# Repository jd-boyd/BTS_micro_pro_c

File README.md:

# BTS_micro_pro_c

## ABOUT

MCU board, mostly with pinout of Arduino Nano Pro, shows up as Leonardo, has USB-C connector.

## LICENSE

* Licensed under CERN-OHL-P v2 or later
* See LICENSE file
* See https://ohwr.org/project/cernohl/wikis/uploads/8a6b5d01f71c207c49493e4d114d61e6/cern_ohl_p_v2_howto.pdf for summary.

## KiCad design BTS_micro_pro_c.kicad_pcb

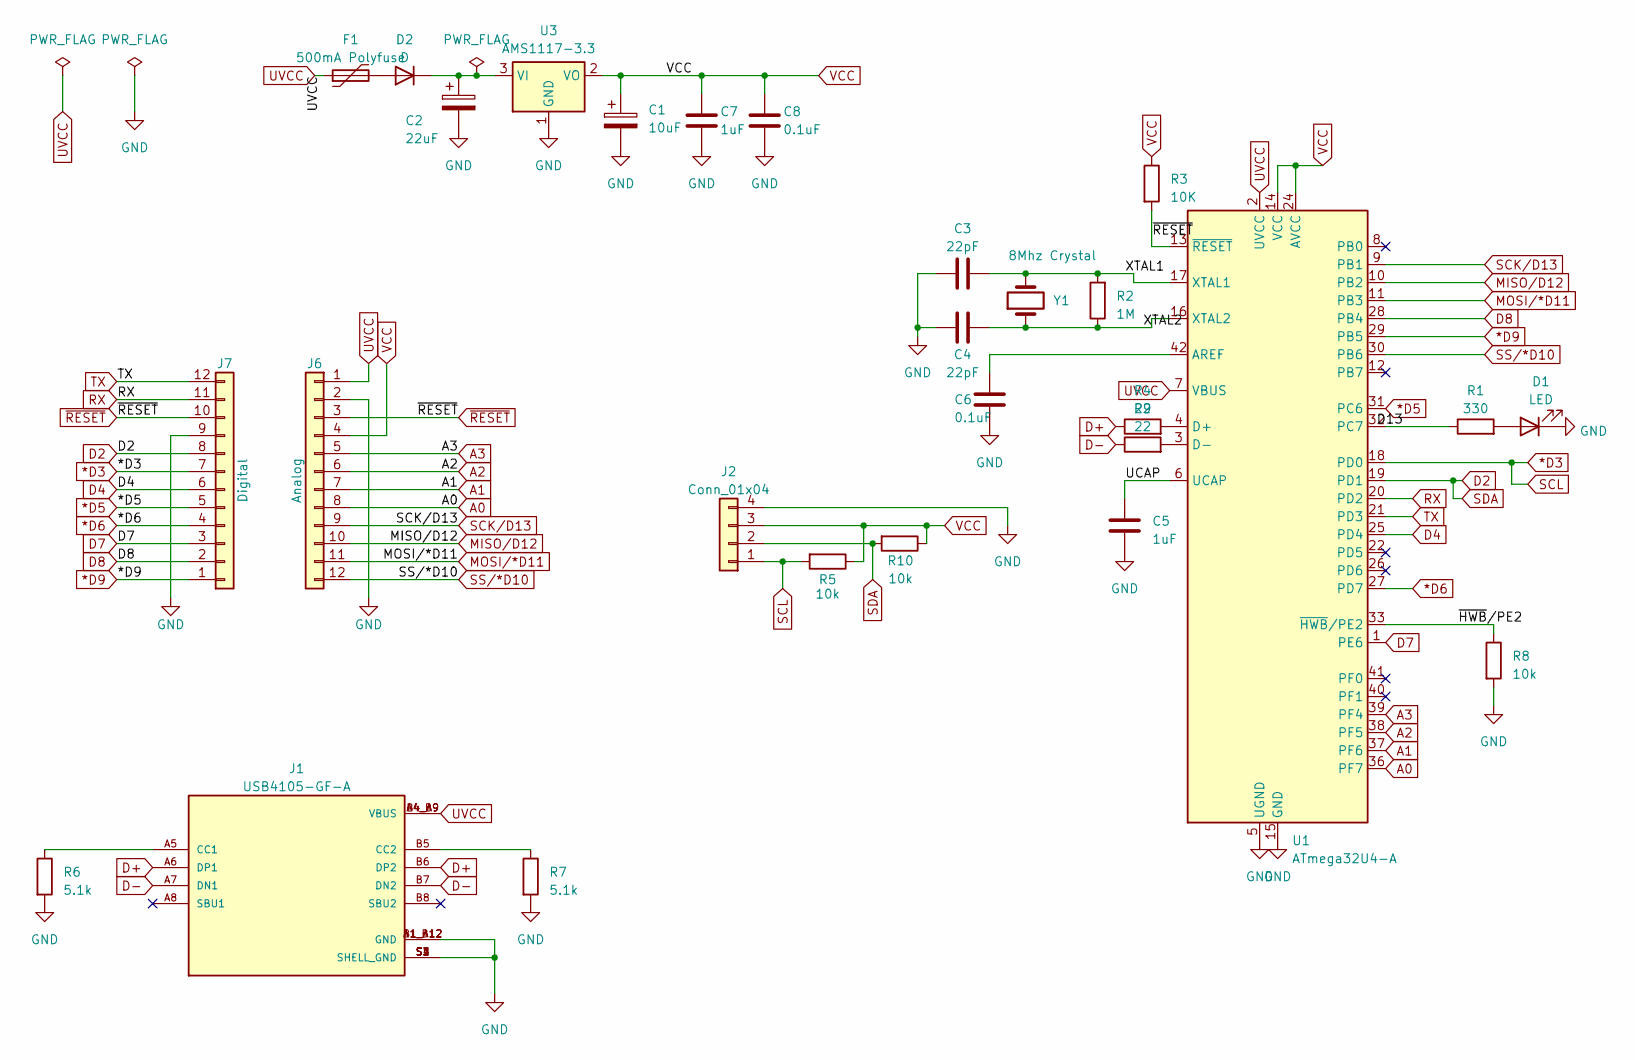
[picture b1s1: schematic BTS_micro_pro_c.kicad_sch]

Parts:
C1: 10uF; C_0402_1005Metric
C2: 22uF; C_0402_1005Metric
C3, C4: 22pF; C_0402_1005Metric
C5, C7: 1uF; C_0402_1005Metric
C6, C8: 0.1uF; C_0402_1005Metric
D1: LED; LED_0402_1005Metric
D2: D; D_0402_1005Metric; LCSC C316041
F1: 500mA Polyfuse; Fuse_0805_2012Metric; LCSC C135331
J1: USB4105-GF-A; GCT_USB4105-GF-A; PARTREV A3; LCSC C165948
J2: Conn_01x04; JST_SH_BM04B-SRSS-TB_1x04-1MP_P1.00mm_Vertical; LCSC C495539
J6: Analog; PinHeader_1x12_P2.54mm_Vertical
J7: Digital; PinHeader_1x12_P2.54mm_Vertical
R1: 330; R_0402_1005Metric
R2: 1M; R_0402_1005Metric
R3: 10K; R_0402_1005Metric
R4, R9: 22; R_0402_1005Metric
R5, R8, R10: 10k; R_0402_1005Metric
R6, R7: 5.1k; R_0402_1005Metric
U1: ATmega32U4-A; QFN-44-1EP_7x7mm_P0.5mm_EP5.2x5.2mm; LCSC C112161
U3: AMS1117-3.3; SOT-23-3; LCSC C5446
Y1: 8Mhz Crystal; Crystal_SMD_3225-2Pin_3.2x2.5mm; LCSC C409345

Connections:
*D3: J2.1, J7.7, R5.2, U1.18 (PD0)
*D5: J7.5, U1.31 (PC6)
*D6: J7.4, U1.27 (PD7)
*D9: J7.1, U1.29 (PB5)
/D13: R1.1, U1.32 (PC7)
/UCAP: C5.1, U1.6 (UCAP)
/XTAL1: C3.2, R2.2, U1.17 (XTAL1), Y1.2
/XTAL2: C4.1, R2.1, U1.16 (XTAL2), Y1.1
/~HWB/PE2: R8.1, U1.33 (~HWB/PE2)
A0: J6.8, U1.36 (PF7)
A1: J6.7, U1.37 (PF6)
A2: J6.6, U1.38 (PF5)
A3: J6.5, U1.39 (PF4)
D2: J2.2, J7.8, R10.2, U1.19 (PD1)
D4: J7.6, U1.25 (PD4)
D7: J7.3, U1.1 (PE6)
D8: J7.2, U1.28 (PB4)
D+: J1.A6 (DP1), J1.B6 (DP2), R4.1
D-: J1.A7 (DN1), J1.B7 (DN2), R9.1
GND: C1.2, C2.2, C3.1, C4.2, C5.2, C6.2, C7.2, C8.2, D1.1 (K), J1.A1_B12 (GND), J1.B1_A12 (GND), J1.S1 (SHELL_GND), J1.S2 (SHELL_GND), J1.S3 (SHELL_GND), J1.S4 (SHELL_GND), J2.4, J6.2, J7.9, R6.2, R7.2, R8.2, U1.5 (UGND), U1.15 (GND), U1.23 (GND), U1.35 (GND), U1.43 (GND), U3.1 (GND)
MISO/D12: J6.10, U1.10 (PB2)
MOSI/*D11: J6.11, U1.11 (PB3)
unnamed: D1.2 (A), R1.2
unnamed: D2.2 (A), F1.2
unnamed: C2.1, D2.1 (K), U3.3 (VI)
unnamed: J1.A5 (CC1), R6.1
unnamed: J1.B5 (CC2), R7.1
unnamed: C6.1, U1.42 (AREF)
unnamed: R4.2, U1.4 (D+)
unnamed: R9.2, U1.3 (D-)
RX: J7.11, U1.20 (PD2)
SCK/D13: J6.9, U1.9 (PB1)
SS/*D10: J6.12, U1.30 (PB6)
TX: J7.12, U1.21 (PD3)
UVCC: F1.1, J1.A4_B9 (VBUS), J1.B4_A9 (VBUS), J6.1, U1.2 (UVCC), U1.7 (VBUS)
VCC: C1.1, C7.1, C8.1, J2.3, J6.4, R3.1, R5.1, R10.1, U1.14 (VCC), U1.24 (AVCC), U1.34 (VCC), U1.44 (AVCC), U3.2 (VO)
~RESET: J6.3, J7.10, R3.2, U1.13 (~RESET)

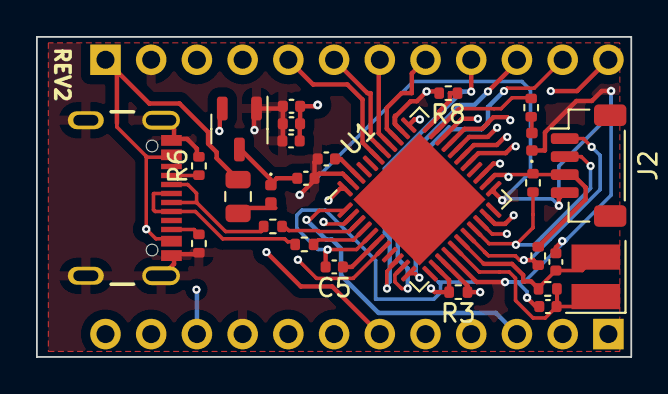
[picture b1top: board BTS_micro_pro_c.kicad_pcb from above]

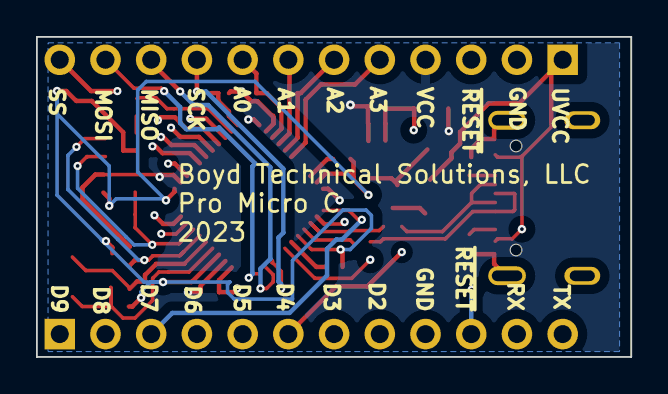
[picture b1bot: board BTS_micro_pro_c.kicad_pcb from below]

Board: 4 copper layers, 33.0 x 17.8 mm, 28 parts (2 on the bottom side), 37 nets.

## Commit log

2023-04-02 Change license to intented one.
2023-04-02 Initial import of KiCAD project.
2023-04-05 Placeholder for changes.
2023-04-05 Start datasheets directory, add cpu.
2023-04-08 More progress.
2023-04-11 Schematic potentially done, needs footprints assigned though.
2023-04-14 Finish rev1.
2023-04-21 Start rev 2.
    In schematic, add USB resistors, put back I2C port.
    Also, fix rotation issue that JLCPCB DFM picked up.
2023-04-25 Update project to rev 2.
    This includes new I2C connector (STEMMA QT), fixed missing resistors on USB, change to easier to route osc.
    Also includes custominng some footprints for space concerns.
